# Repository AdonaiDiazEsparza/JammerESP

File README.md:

# JammerESP
This is a repository for a Jammer created with esp32, this is for education purpose

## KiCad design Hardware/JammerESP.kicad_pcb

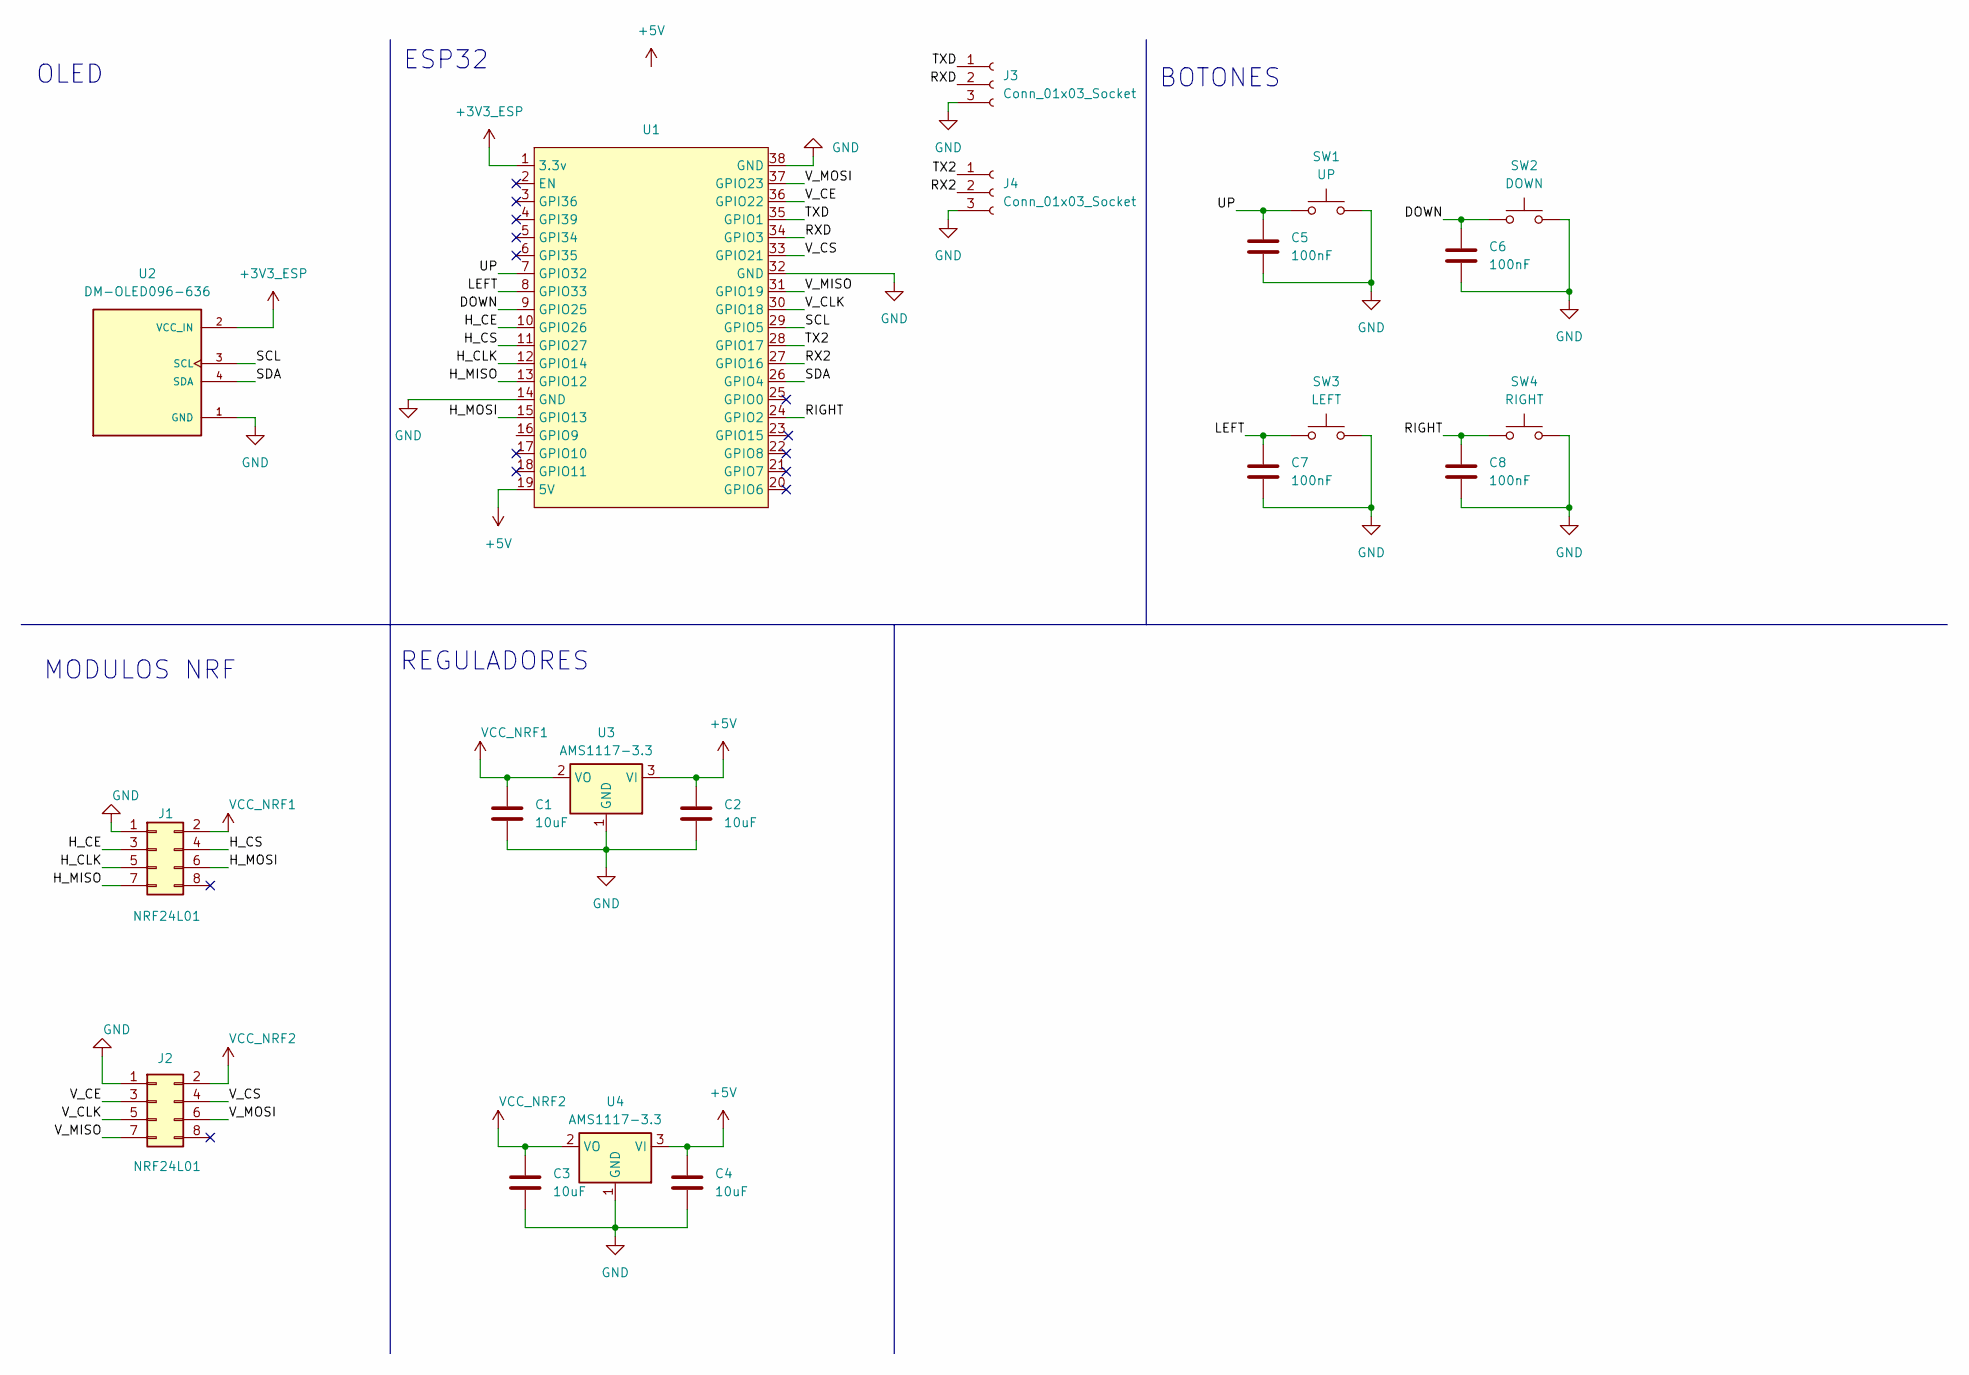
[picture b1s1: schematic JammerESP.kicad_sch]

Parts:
C1, C2, C3, C4: 10uF; C_1206_3216Metric_Pad1.33x1.80mm_HandSolder
C5, C6, C7, C8: 100nF; C_1206_3216Metric_Pad1.33x1.80mm_HandSolder
J1, J2: NRF24L01; PinHeader_2x04_P2.54mm_Vertical
J3, J4: Conn_01x03_Socket; PinHeader_1x03_P2.54mm_Vertical
SW1: UP; SW_BUTT-2
SW2: DOWN; SW_BUTT-2
SW3: LEFT; SW_BUTT-2
SW4: RIGHT; SW_BUTT-2
U1: Z_ESP32_DevKitC_38pin_socket
U2: DM-OLED096-636; MODULE_DM-OLED096-636; PARTREV 2018-09-10
U3, U4: AMS1117-3.3; SOT-223-3_TabPin2

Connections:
+3V3_ESP: U1.1 (3.3v), U2.2 (VCC_IN)
+5V: C2.1, C4.1, U1.19 (5V), U3.3 (VI), U4.3 (VI)
/DOWN: C6.1, SW2.1, U1.9 (GPIO25)
/H_CE: J1.3, U1.10 (GPIO26)
/H_CLK: J1.5, U1.12 (GPIO14)
/H_CS: J1.4, U1.11 (GPIO27)
/H_MISO: J1.7, U1.13 (GPIO12)
/H_MOSI: J1.6, U1.15 (GPIO13)
/LEFT: C7.1, SW3.1, U1.8 (GPIO33)
/RIGHT: C8.1, SW4.1, U1.24 (GPIO2)
/RX2: J4.2, U1.27 (GPIO16)
/RXD: J3.2, U1.34 (GPIO3)
/SCL: U1.29 (GPIO5), U2.3 (SCL)
/SDA: U1.26 (GPIO4), U2.4 (SDA)
/TX2: J4.1, U1.28 (GPIO17)
/TXD: J3.1, U1.35 (GPIO1)
/UP: C5.1, SW1.1, U1.7 (GPIO32)
/V_CE: J2.3, U1.36 (GPIO22)
/V_CLK: J2.5, U1.30 (GPIO18)
/V_CS: J2.4, U1.33 (GPIO21)
/V_MISO: J2.7, U1.31 (GPIO19)
/V_MOSI: J2.6, U1.37 (GPIO23)
GND: C1.2, C2.2, C3.2, C4.2, C5.2, C6.2, C7.2, C8.2, J1.1, J2.1, J3.3, J4.3, SW1.2, SW2.2, SW3.2, SW4.2, U1.14 (GND), U1.32 (GND), U1.38 (GND), U2.1 (GND), U3.1 (GND), U4.1 (GND)
VCC_NRF1: C1.1, J1.2, U3.2 (VO)
VCC_NRF2: C3.1, J2.2, U4.2 (VO)

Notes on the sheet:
MODULOS NRF
REGULADORES
BOTONES
ESP32
OLED

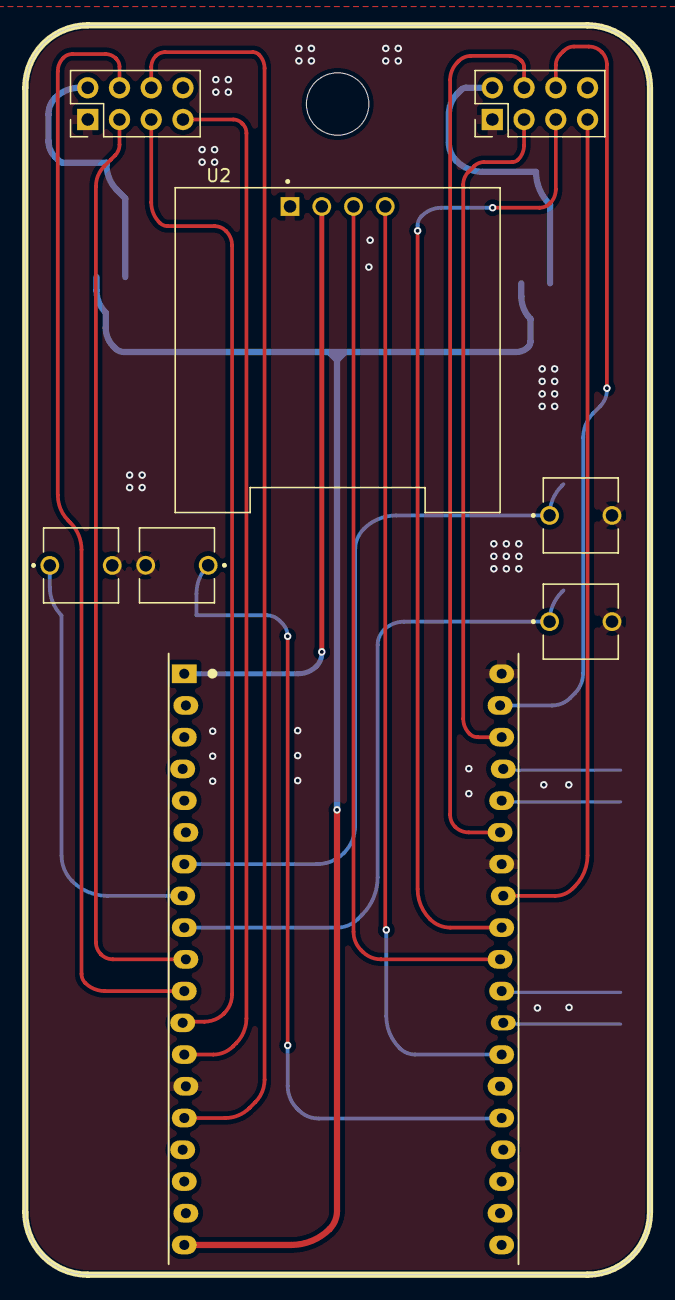
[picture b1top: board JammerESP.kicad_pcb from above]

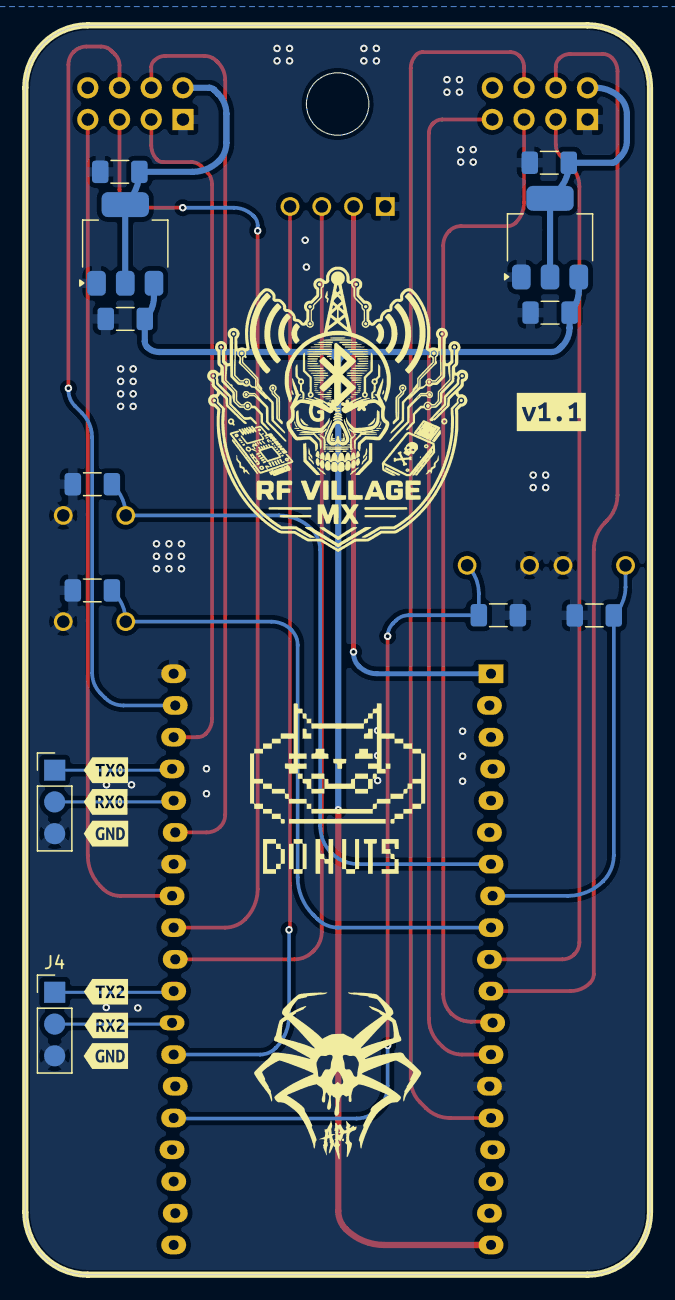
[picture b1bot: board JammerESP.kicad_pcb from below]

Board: 2 copper layers, 50.0 x 100.0 mm, 27 parts (19 on the bottom side), 25 nets.

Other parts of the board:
kibuzzard-6AEBD6AF: G***; kibuzzard-6AEBD6AF
kibuzzard-6AEBD6E6: G***; kibuzzard-6AEBD6E6
kibuzzard-6AEBD6F6: G***; kibuzzard-6AEBD6F6
kibuzzard-6AEBD705: G***; kibuzzard-6AEBD705
kibuzzard-6AECB2F5: G***; kibuzzard-6AECB2F5
kibuzzard-6AECB2FA: G***; kibuzzard-6AECB2FA
kibuzzard-6AECB298: G***; kibuzzard-6AECB298

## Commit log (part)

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2026-01-06 feat: add files for proyect
2026-05-23 update firmware
2026-05-28 feat: add text for jammer
2026-06-09 Move firmware files to firmware folder
2026-06-09 add schematic
2026-06-10 add pcb design
2026-06-10 feat: put capacitors and check battery dimension
2026-06-24 Add routes
2026-06-25 update routes
